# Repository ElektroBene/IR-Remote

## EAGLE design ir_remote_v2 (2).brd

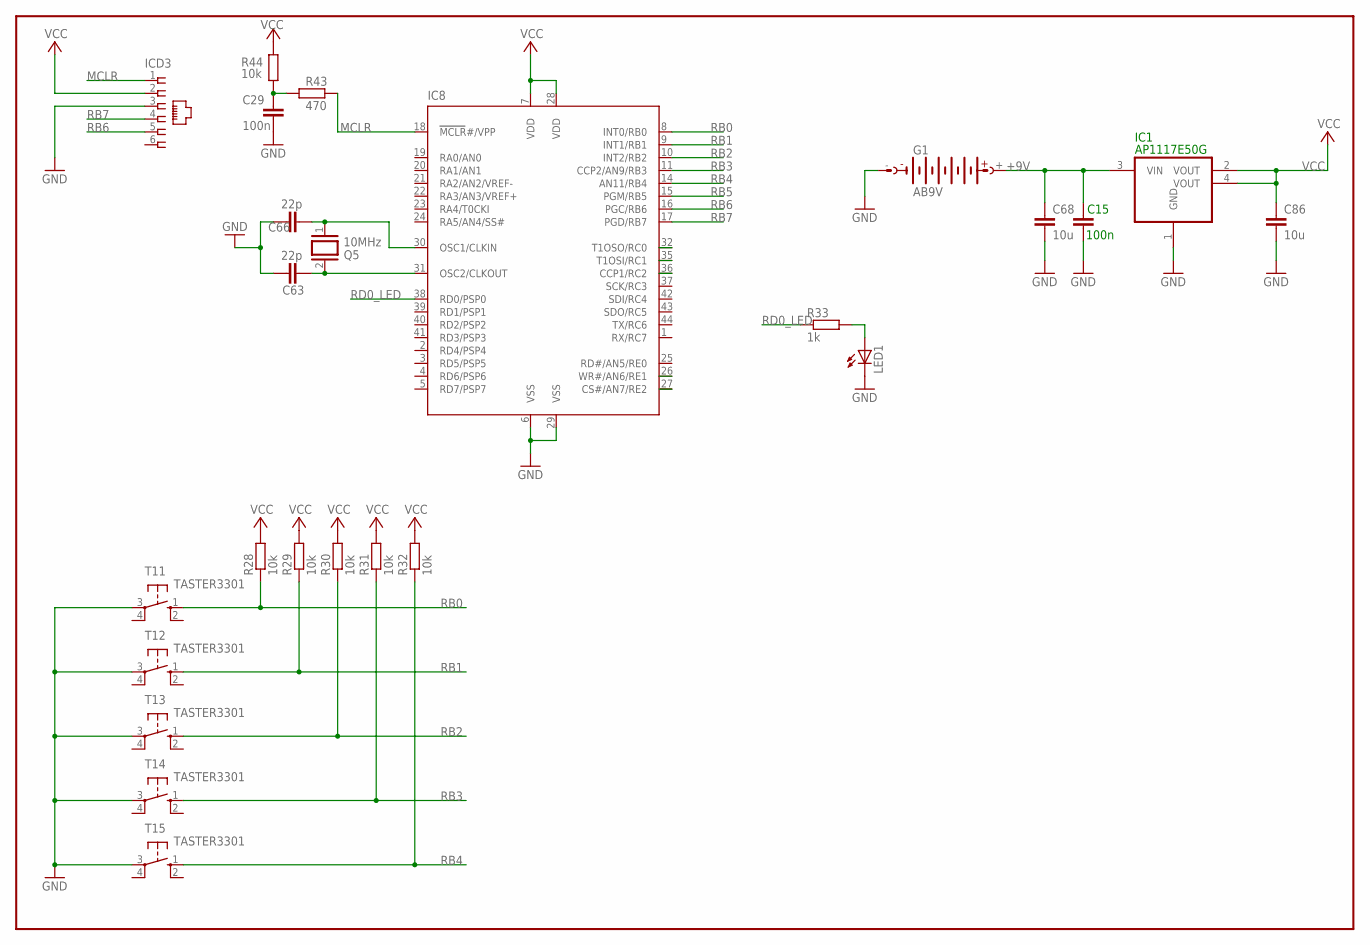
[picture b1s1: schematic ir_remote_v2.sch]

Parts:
C15, C29: 100n; C0805
C63, C66: 22p; C0603_WE
C68, C86: 10u; C0805
G1: AB9V
IC1: AP1117E50G; SOT223
IC8: PIC18F4520; TQFP44
ICD3: 520250-3
LED1: LED5MM
Q5: 10MHz; QUARZ_HC5032/2
R28, R29, R30, R31, R32: 10k; 0207/7
R33: 1k; 0207/10
R43: 470; M0805
R44: 10k; M0805
T11, T12, T13, T14, T15: TASTER3301

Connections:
+9V: C15.1, C68.1, G1.+, IC1.3 (VIN)
D0_LCD: IC8.27 (CS#/AN7/RE2)
D1_LCD: IC8.26 (WR#/AN6/RE1)
GND: C15.2, C29.2, C63.1, C66.1, C68.2, C86.2, G1.-, IC1.1 (GND), IC8.6 (VSS), IC8.29 (VSS), ICD3.3, LED1.K (C), T11.3, T12.3, T13.3, T14.3, T15.3
MCLR: IC8.18 (MCLR#/VPP), ICD3.1, R43.1
unnamed: LED1.A, R33.2
unnamed: C29.1, R43.2, R44.2
unnamed: C66.2, IC8.30 (OSC1/CLKIN), Q5.1
unnamed: C63.2, IC8.31 (OSC2/CLKOUT), Q5.2
RB0: IC8.8 (INT0/RB0), R28.1, T11.1 (S)
RB1: IC8.9 (INT1/RB1), IC8.35 (T1OSI/RC1), R29.1, T12.1 (S)
RB2: IC8.10 (INT2/RB2), IC8.32 (T1OSO/RC0), R30.1, T13.1 (S)
RB3: IC8.11 (CCP2/AN9/RB3), R31.1, T14.1 (S)
RB4: IC8.14 (AN11/RB4), R32.1, T15.1 (S)
RB5: IC8.15 (PGM/RB5)
RB6: IC8.16 (PGC/RB6), ICD3.5
RB7: IC8.17 (PGD/RB7), ICD3.4
RD0_LED: IC8.38 (RD0/PSP0), R33.1
RDS_INT: IC8.36 (CCP1/RC2)
VCC: C86.1, IC1.2 (VOUT), IC1.4 (VOUT), IC8.7 (VDD), IC8.28 (VDD), ICD3.2, R28.2, R29.2, R30.2, R31.2, R32.2, R44.1

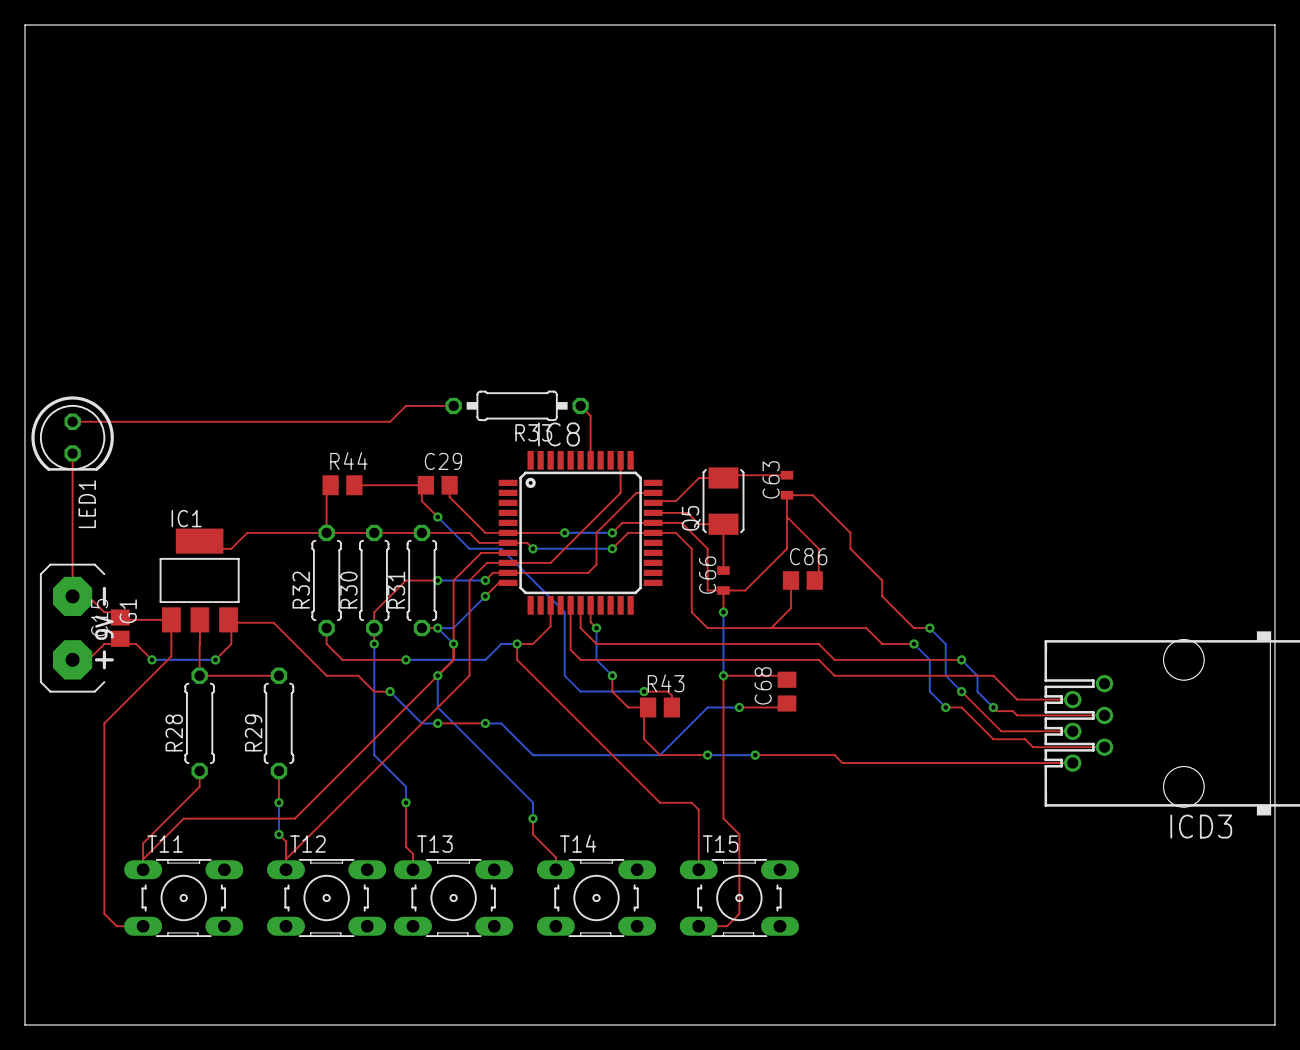
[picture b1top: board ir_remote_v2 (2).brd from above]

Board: 2 copper layers, 100.0 x 80.0 mm, 25 parts (0 on the bottom side), 16 nets.

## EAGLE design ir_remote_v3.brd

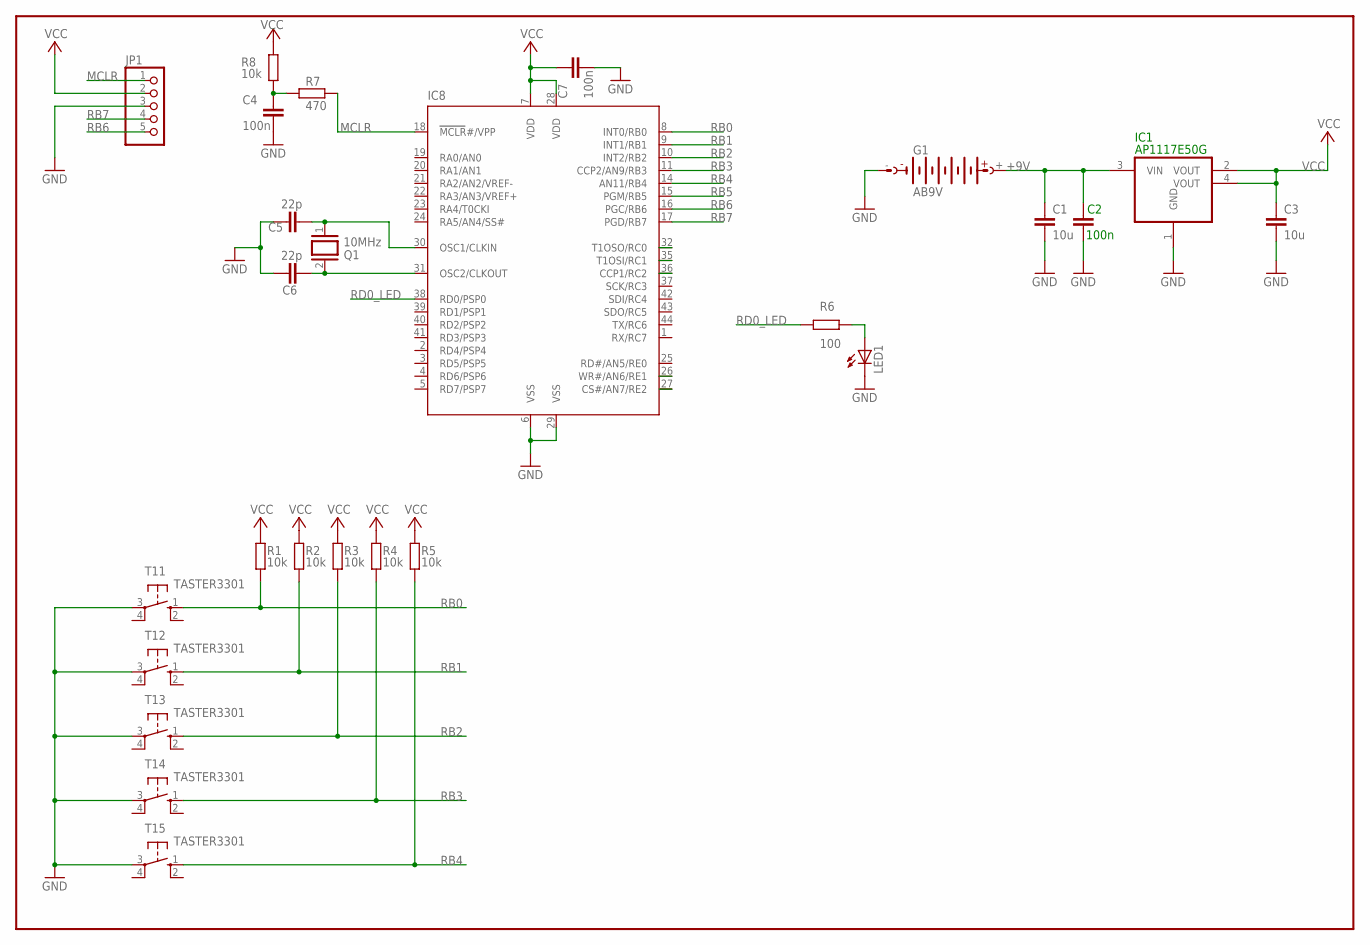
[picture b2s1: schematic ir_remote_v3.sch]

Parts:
C1, C3: 10u; C0805
C2, C4, C7: 100n; C0805
C5, C6: 22p; C0603_WE
G1: AB9V
IC1: AP1117E50G; SOT223
IC8: PIC18F4520; TQFP44
JP1: PINHD-1X5; 1X05
LED1: LED5MM
Q1: 10MHz; QUARZ_HC5032/2
R1, R2, R3, R4, R5, R8: 10k; M0805
R6: 100; M0805
R7: 470; M0805
T11, T12, T13, T14, T15: TASTER3301

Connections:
+9V: C1.1, C2.1, G1.+, IC1.3 (VIN)
D0_LCD: IC8.27 (CS#/AN7/RE2)
D1_LCD: IC8.26 (WR#/AN6/RE1)
GND: C1.2, C2.2, C3.2, C4.2, C5.1, C6.1, C7.2, G1.-, IC1.1 (GND), IC8.6 (VSS), IC8.29 (VSS), JP1.3, LED1.K (C), T11.3, T12.3, T13.3, T14.3, T15.3
MCLR: IC8.18 (MCLR#/VPP), JP1.1, R7.1
unnamed: LED1.A, R6.2
unnamed: C4.1, R7.2, R8.2
unnamed: C5.2, IC8.30 (OSC1/CLKIN), Q1.1
unnamed: C6.2, IC8.31 (OSC2/CLKOUT), Q1.2
RB0: IC8.8 (INT0/RB0), R1.2, T11.1 (S)
RB1: IC8.9 (INT1/RB1), IC8.35 (T1OSI/RC1), R2.2, T12.1 (S)
RB2: IC8.10 (INT2/RB2), IC8.32 (T1OSO/RC0), R3.2, T13.1 (S)
RB3: IC8.11 (CCP2/AN9/RB3), R4.2, T14.1 (S)
RB4: IC8.14 (AN11/RB4), R5.2, T15.1 (S)
RB5: IC8.15 (PGM/RB5)
RB6: IC8.16 (PGC/RB6), JP1.5
RB7: IC8.17 (PGD/RB7), JP1.4
RD0_LED: IC8.38 (RD0/PSP0), R6.1
RDS_INT: IC8.36 (CCP1/RC2)
VCC: C3.1, C7.1, IC1.2 (VOUT), IC1.4 (VOUT), IC8.7 (VDD), IC8.28 (VDD), JP1.2, R1.1, R2.1, R3.1, R4.1, R5.1, R8.1

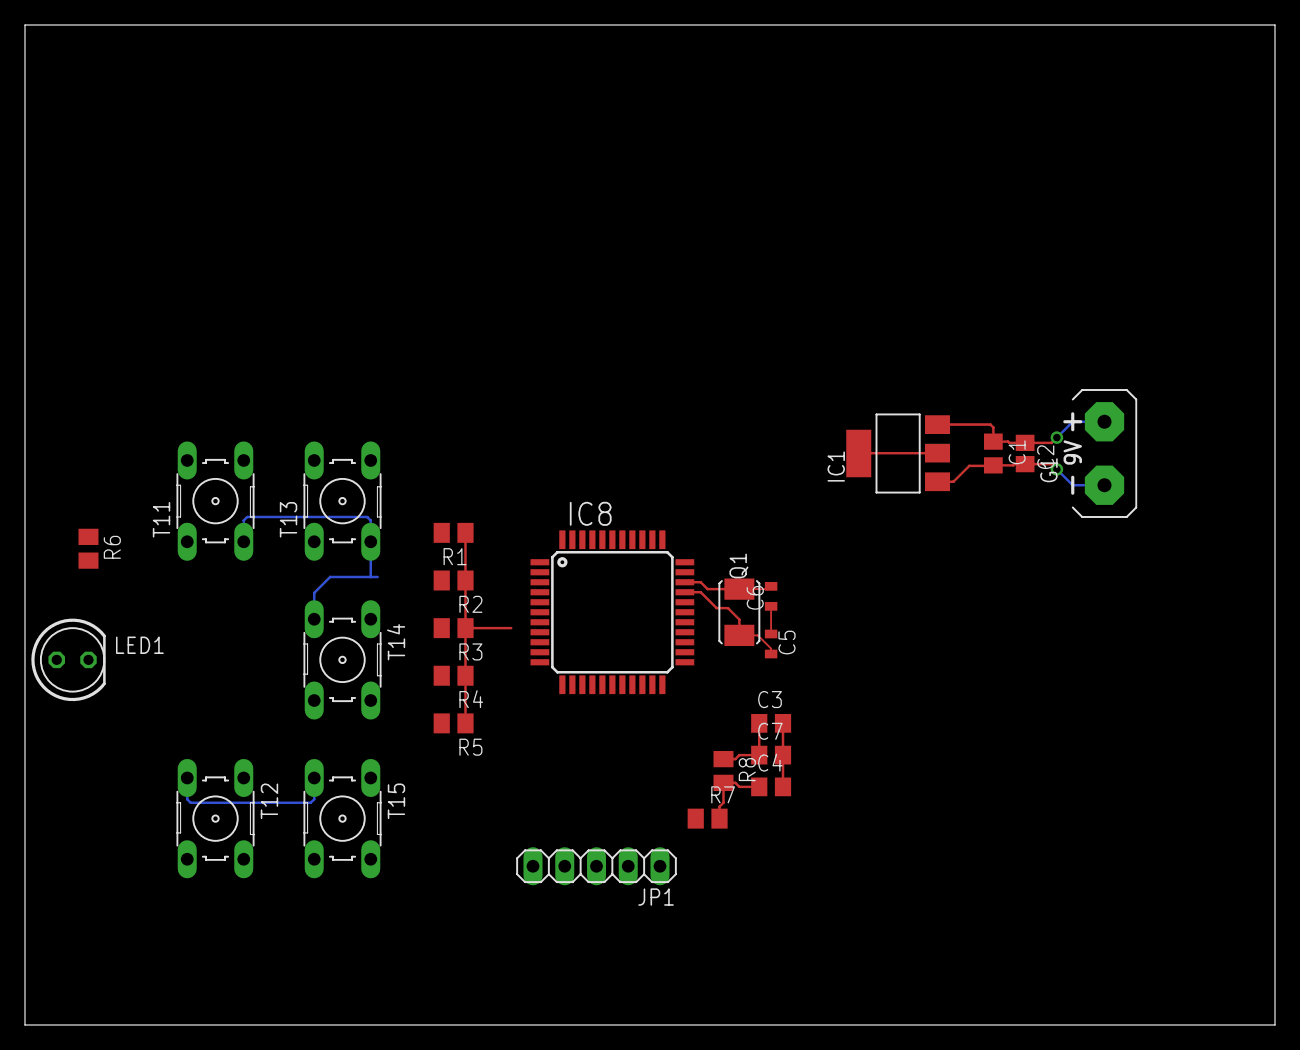
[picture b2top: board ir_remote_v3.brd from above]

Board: 2 copper layers, 100.0 x 80.0 mm, 26 parts (0 on the bottom side), 16 nets.
